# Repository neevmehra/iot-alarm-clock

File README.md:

# ECE445L Lab 4E - IoT Alarm Clock with MQTT and ESP8266

An embedded IoT alarm clock built on the **TM4C123 LaunchPad** with an **ESP8266 Wi-Fi module**, **MQTT-based communication**, and a **web application interface**. This project extends a prior clock system by enabling real-time remote monitoring and control over Wi-Fi.

## Overview
This project implements a “smart object” that publishes clock state to an MQTT broker and receives control commands from a web application. The system bridges embedded firmware, UART communication, Wi-Fi networking, and a browser-based frontend.

## Features
- Real-time clock displayed on the ST7735 LCD
- Remote control through MQTT publish/subscribe
- ESP8266 used as the Wi-Fi bridge between the TM4C123 and the broker
- Web app with clock controls:
  - Hour++
  - Hour--
  - Minute++
  - Minute--
  - Second++
  - Second--
  - Toggle 12/24-hour mode
- UART-based communication between TM4C123 and ESP8266
- Periodic state publishing from the board to the web app
- Subscription handling for incoming web commands
- Reuse and extension of prior clock/alarm functionality

## System Architecture
The data flow is:

TM4C123 -> UART -> ESP8266 -> Wi-Fi -> MQTT Broker -> Web App  
Web App -> MQTT Broker -> ESP8266 -> UART -> TM4C123

The TM4C publishes time data, and the web app sends back control commands using MQTT topics scoped to the user/team EID.

## Hardware
- TI EK-TM4C123GXL LaunchPad
- ESP8266-ESP01
- ST7735 TFT LCD
- External 3.3V regulator for ESP8266
- Switches
- Speaker / alarm hardware reused from Lab 3
- Supporting resistors, capacitors, MOSFET, diode, and wiring

## Software Components
### Embedded firmware
- TM4C123 firmware in C
- UART interface to ESP8266
- MQTT serialization/parsing support
- Clock/alarm logic and LCD update routines

### ESP8266 firmware
- Arduino-based firmware
- Wi-Fi connection handling
- MQTT broker connection
- Topic subscription and publication
- UART bridge between LaunchPad and MQTT broker

### Web application
- HTML / JavaScript MQTT client
- WebSocket-based broker communication
- Live time display and command buttons

## MQTT Interface
Example topic structure:

- `<eid>/b2w/mode`
- `<eid>/b2w/hour`
- `<eid>/b2w/min`
- `<eid>/b2w/sec`
- `<eid>/w2b`

Where:
- `b2w` = board to web
- `w2b` = web to board

## Key Technical Work
- Configured UART5 communication between the TM4C123 and ESP8266
- Modified parser logic for web-to-board commands
- Built CSV-based data transfer from TM4C firmware to the ESP8266
- Extended a browser MQTT app for remote clock control
- Integrated Lab 3 clock behavior into a networked IoT system
- Debugged timing, subscriptions, and state synchronization across devices

## Validation
This project was validated by:
- confirming broker connection from the ESP8266
- verifying topic publish/subscribe behavior
- checking synchronized updates on both the LCD and web interface
- testing remote control actions from the web app
- observing UART/debug output and timing behavior

## Repository Structure
```text
src/        TM4C123 firmware
esp/        ESP8266 Arduino code
web/        MQTT web application
docs/       images, diagrams, report assets
project/    Keil or IDE project files

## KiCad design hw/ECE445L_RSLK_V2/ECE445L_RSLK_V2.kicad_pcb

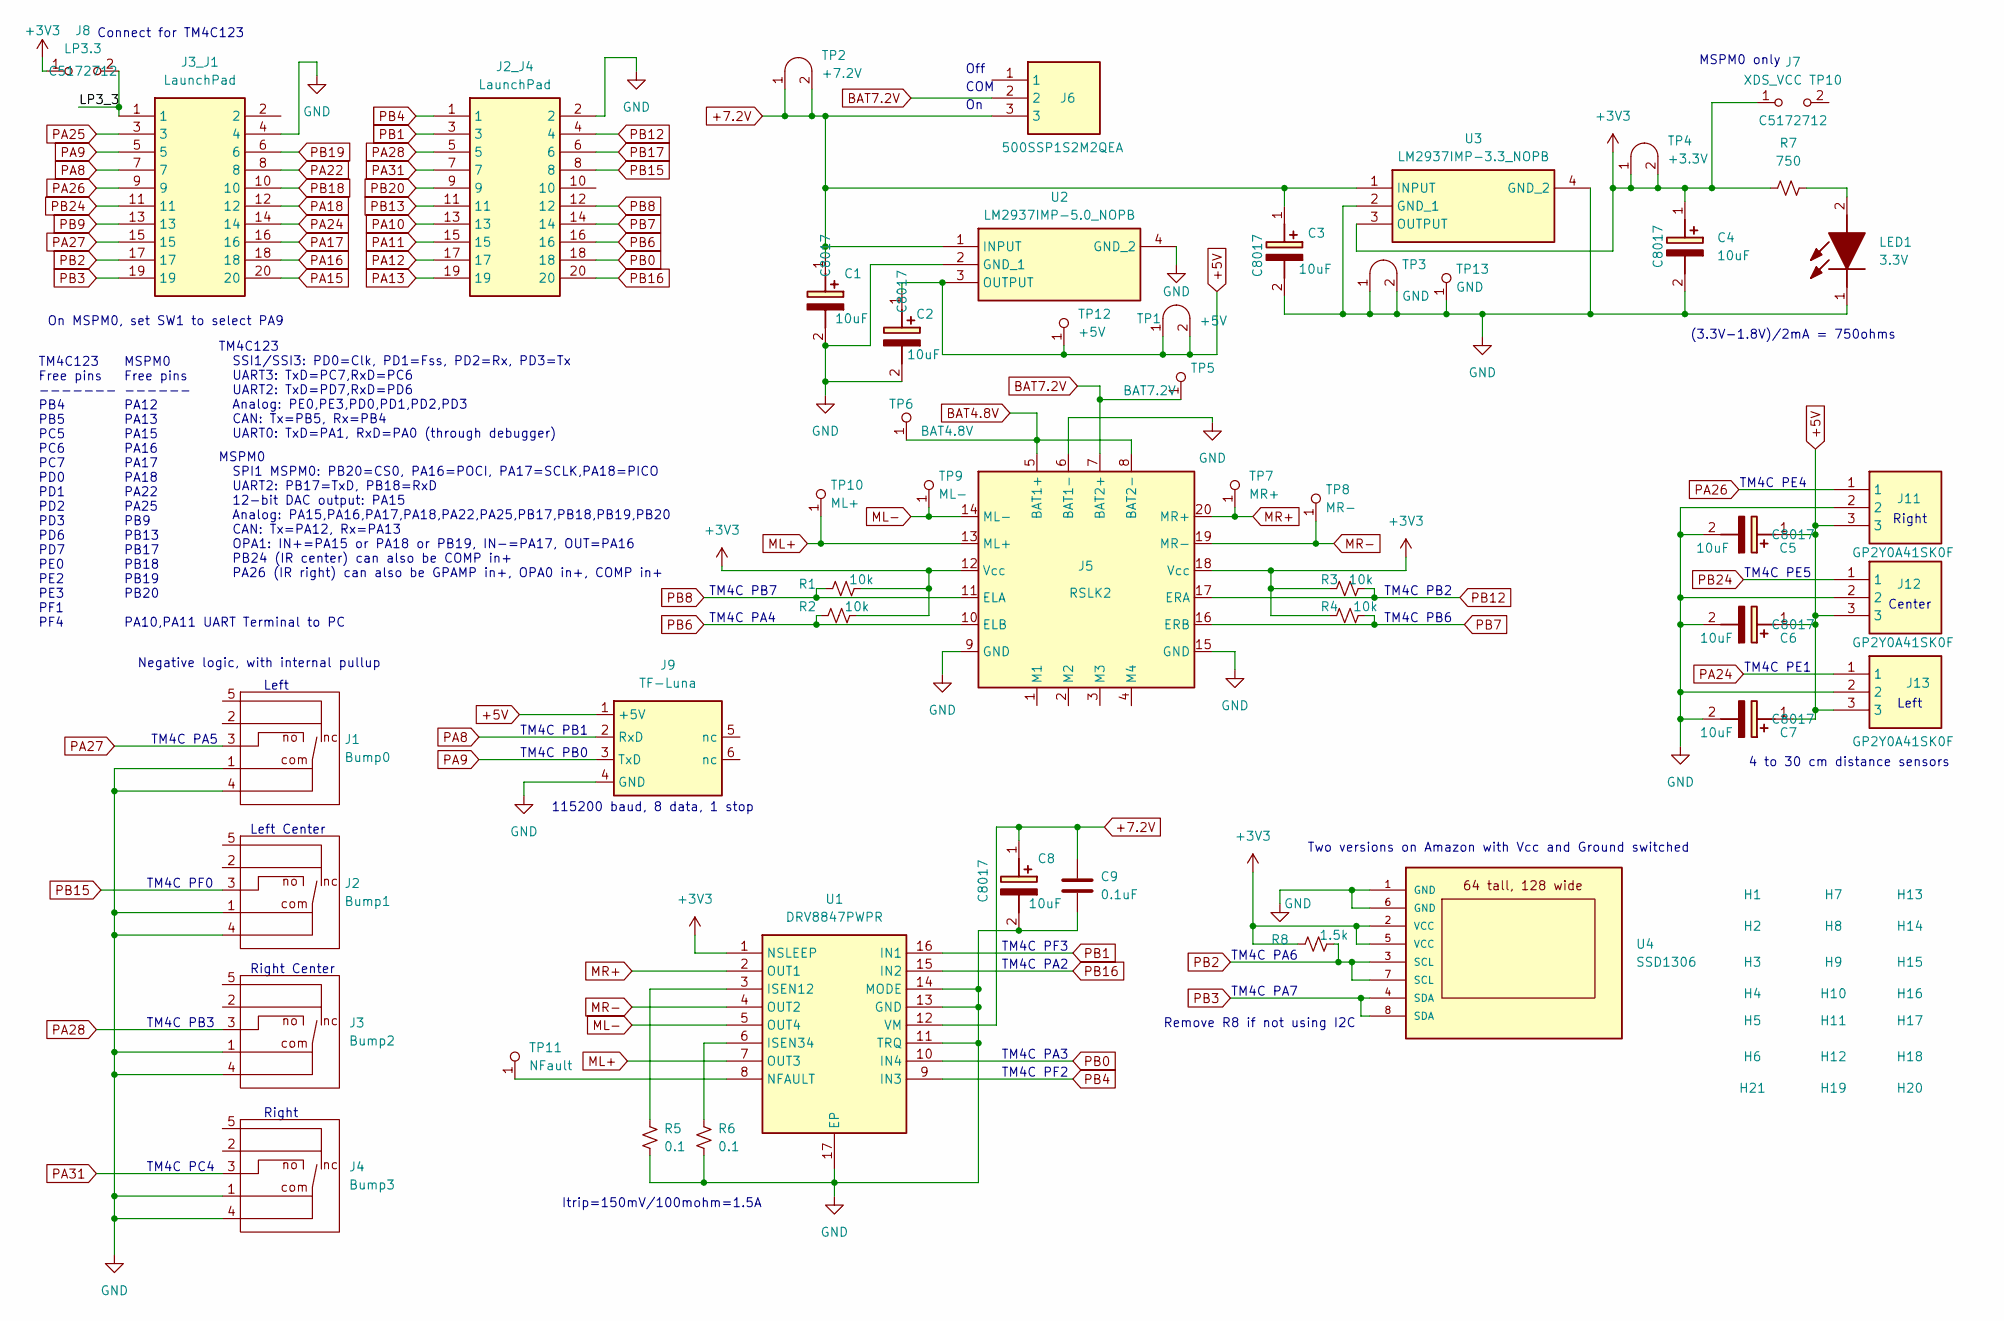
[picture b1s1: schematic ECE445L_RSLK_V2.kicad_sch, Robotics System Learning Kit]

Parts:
C1, C2, C3, C4, C5, C6, C7, C8: 10uF; CAPPM3528X210N; Mouser Part Number 581-TAJB106K020R
C9: 0.1uF; C_0603_1608Metric; LCSC C5186689
H1, H2, H3, H4, H5, H6, H7, H8, H9, H10, H11, H12, H13, H14, H15, H16, H17, H18, H19, H20, H21: MountingHole_4_40
J1: Bump0; D2F-01L30-D3_5pin
J2: Bump1; D2F-01L30-D3_5pin
J2_J4, J3_J1: LaunchPad; Mouser Part Number 855-M20-8761042P
J3: Bump2; D2F-01L30-D3_5pin
J4: Bump3; D2F-01L30-D3_5pin
J5: RSLK2; RSLK_Chassis
J6: 500SSP1S2M2QEA; Mouser Part Number 612-500SSP1S2M2QEA
J7: XDS_VCC TP10; PinHeader_1x02_P2.54mm_Vertical; LCSC C5172712
J8: LP3.3; PinHeader_1x02_P2.54mm_Vertical; LCSC C5172712
J9: TF-Luna; JST-GH_1x06_1.25mm
J11, J12, J13: GP2Y0A41SK0F; SHDR3W50P0X200_1X3_650X240X440P; Mouser Part Number 855-M22-7130342
LED1: 3.3V; APT1608CGCK; Mouser Part Number 604-APTD1608LSECKJ3F
R1, R2, R3, R4: 10k; R_0603_1608Metric; LCSC C340542
R5, R6: 0.1; R_1206_3216Metric; LCSC C2889036
R7: 750; R_0603_1608Metric; LCSC C365210
R8: 1.5k; R_0603_1608Metric; LCSC C216914
TP1: +5V; Testpoint_1x02_P2.54mm
TP2: +7.2V; Testpoint_1x02_P2.54mm
TP3: GND; Testpoint_1x02_P2.54mm
TP4: +3.3V; Testpoint_1x02_P2.54mm
TP5: BAT7.2V; Testpoint_1x1
TP6: BAT4.8V; Testpoint_1x1
TP7: MR+; Testpoint_1x1
TP8: MR-; Testpoint_1x1
TP9: ML-; Testpoint_1x1
TP10: ML+; Testpoint_1x1
TP11: NFault; Testpoint_1x1
TP12: +5V; Testpoint_1x1
TP13: GND; Testpoint_1x1
U1: DRV8847PWPR; SOP65P640X120-17N; Mouser Part Number 595-DRV8847PWPR
U2: LM2937IMP-5.0_NOPB; SOT230P700X180-4N; Mouser Part Number 926-LM2937IMP5.0NOPB
U3: LM2937IMP-3.3_NOPB; SOT230P700X180-4N; Mouser Part Number 926-LM2937IMP3.3NOPB
U4: SSD1306

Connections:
+3V3: C4.1 (+), J5.12 (Vcc), J5.18 (Vcc), J7.1 (A), J8.1 (A), R1.2, R2.2, R3.1, R4.1, R7.2, R8.1, TP4.1 (A), TP4.2 (B), U1.1 (NSLEEP), U3.3 (OUTPUT), U4.2 (VCC), U4.5 (VCC)
+5V: C2.1 (+), C5.1 (+), C6.1 (+), C7.1 (+), J9.1 (+5V), J11.3, J12.3, J13.3, TP1.1 (A), TP1.2 (B), TP12.1 (A), U2.3 (OUTPUT)
+7.2V: C1.1 (+), C3.1 (+), C8.1 (+), C9.1, J6.3, TP2.1 (A), TP2.2 (B), U1.12 (VM), U2.1 (INPUT), U3.1 (INPUT)
/LP3_3: J3_J1.1, J8.2 (B)
BAT4.8V: J5.5 (BAT1+), J5.8 (BAT2-), TP6.1 (A)
BAT7.2V: J5.7 (BAT2+), J6.2, TP5.1 (A)
GND: C1.2 (-), C2.2 (-), C3.2 (-), C4.2 (-), C5.2 (-), C6.2 (-), C7.2 (-), C8.2 (-), C9.2, J1.1 (com), J1.4 (com), J2.1 (com), J2.4 (com), J2_J4.2, J3.1 (com), J3.4 (com), J3_J1.4, J4.1 (com), J4.4 (com), J5.6 (BAT1-), J5.9 (GND), J5.15 (GND), J9.4 (GND), J11.2, J12.2, J13.2, LED1.1 (K), R5.2, R6.2, TP3.1 (A), TP3.2 (B), TP13.1 (A), U1.11 (TRQ), U1.13 (GND), U1.14 (MODE), U1.17 (EP), U2.2 (GND_1), U2.4 (GND_2), U3.2 (GND_1), U3.4 (GND_2), U4.1 (GND), U4.6 (GND)
ML+: J5.13 (ML+), TP10.1 (A), U1.7 (OUT3)
ML-: J5.14 (ML-), TP9.1 (A), U1.5 (OUT4)
MR+: J5.20 (MR+), TP7.1 (A), U1.2 (OUT1)
MR-: J5.19 (MR-), TP8.1 (A), U1.4 (OUT2)
unnamed: LED1.2 (A), R7.1
unnamed: TP11.1 (A), U1.8 (NFAULT)
unnamed: R5.1, U1.3 (ISEN12)
unnamed: R6.1, U1.6 (ISEN34)
PA8: J3_J1.7, J9.2 (RxD)
PA9: J3_J1.5, J9.3 (TxD)
PA10: J2_J4.13
PA11: J2_J4.15
PA12: J2_J4.17
PA13: J2_J4.19
PA15: J3_J1.20
PA16: J3_J1.18
PA17: J3_J1.16
PA18: J3_J1.12
PA22: J3_J1.8
PA24: J3_J1.14, J13.1
PA25: J3_J1.3
PA26: J3_J1.9, J11.1
PA27: J1.3 (no), J3_J1.15
PA28: J2_J4.5, J3.3 (no)
PA31: J2_J4.7, J4.3 (no)
PB0: J2_J4.18, U1.10 (IN4)
PB1: J2_J4.3, U1.16 (IN1)
PB2: J3_J1.17, R8.2, U4.3 (SCL), U4.7 (SCL)
PB3: J3_J1.19, U4.4 (SDA), U4.8 (SDA)
PB4: J2_J4.1, U1.9 (IN3)
PB6: J2_J4.16, J5.10 (ELB), R2.1
PB7: J2_J4.14, J5.16 (ERB), R4.2
PB8: J2_J4.12, J5.11 (ELA), R1.1
PB9: J3_J1.13
PB12: J2_J4.4, J5.17 (ERA), R3.2
PB13: J2_J4.11
PB15: J2.3 (no), J2_J4.8
PB16: J2_J4.20, U1.15 (IN2)
PB17: J2_J4.6
PB18: J3_J1.10
PB19: J3_J1.6
PB20: J2_J4.9
PB24: J3_J1.11, J12.1

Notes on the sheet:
TM4C PB7
TM4C PE5
Negative logic, with internal pullup
TM4C PF2
TM4C PC4
115200 baud, 8 data, 1 stop
Right
TM4C PA3
MSPM0 Free pins ------ PA12 PA13 PA15 PA16 PA17 PA18 PA22 PA25 PB9 PB13 PB17 PB18 PB19 PB20 PA10,PA11 UART Terminal to PC
TM4C PB2
TM4C123 Free pins ------- PB4 PB5 PC5 PC6 PC7 PD0 PD1 PD2 PD3 PD6 PD7 PE0 PE2 PE3 PF1 PF4
TM4C PA4
Left Center
Connect for TM4C123
Left
TM4C PF3
TM4C PA6
MSPM0 SPI1 MSPM0: PB20=CS0, PA16=POCI, PA17=SCLK,PA18=PICO UART2: PB17=TxD, PB18=RxD 12-bit DAC output: PA15 Analog: PA15,PA16,PA17,PA18,PA22,PA25,PB17,PB18,PB19,PB20 CAN: Tx=PA12, Rx=PA13 OPA1: IN+=PA15 or PA18 or PB19, IN-=PA17, OUT=PA16 PB24 (IR center) can also be COMP in+ PA26 (IR right) can a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
TM4C PB1
TM4C PF0
Two versions on Amazon with Vcc and Ground switched
Itrip=150mV/100mohm=1.5A
TM4C PA5
Off
4 to 30 cm distance sensors
TM4C PB6
On MSPM0, set SW1 to select PA9
Remove R8 if not using I2C
TM4C PB0
Right Center
Center
TM4C PE4
(3.3V-1.8V)/2mA = 750ohms
TM4C PB3
TM4C PA7
MSPM0 only
COM
TM4C PE1
TM4C PA2
TM4C123 SSI1/SSI3: PD0=Clk, PD1=Fss, PD2=Rx, PD3=Tx UART3: TxD=PC7,RxD=PC6 UART2: TxD=PD7,RxD=PD6 Analog: PE0,PE3,PD0,PD1,PD2,PD3 CAN: Tx=PB5, Rx=PB4 UART0: TxD=PA1, RxD=PA0 (through debugger)

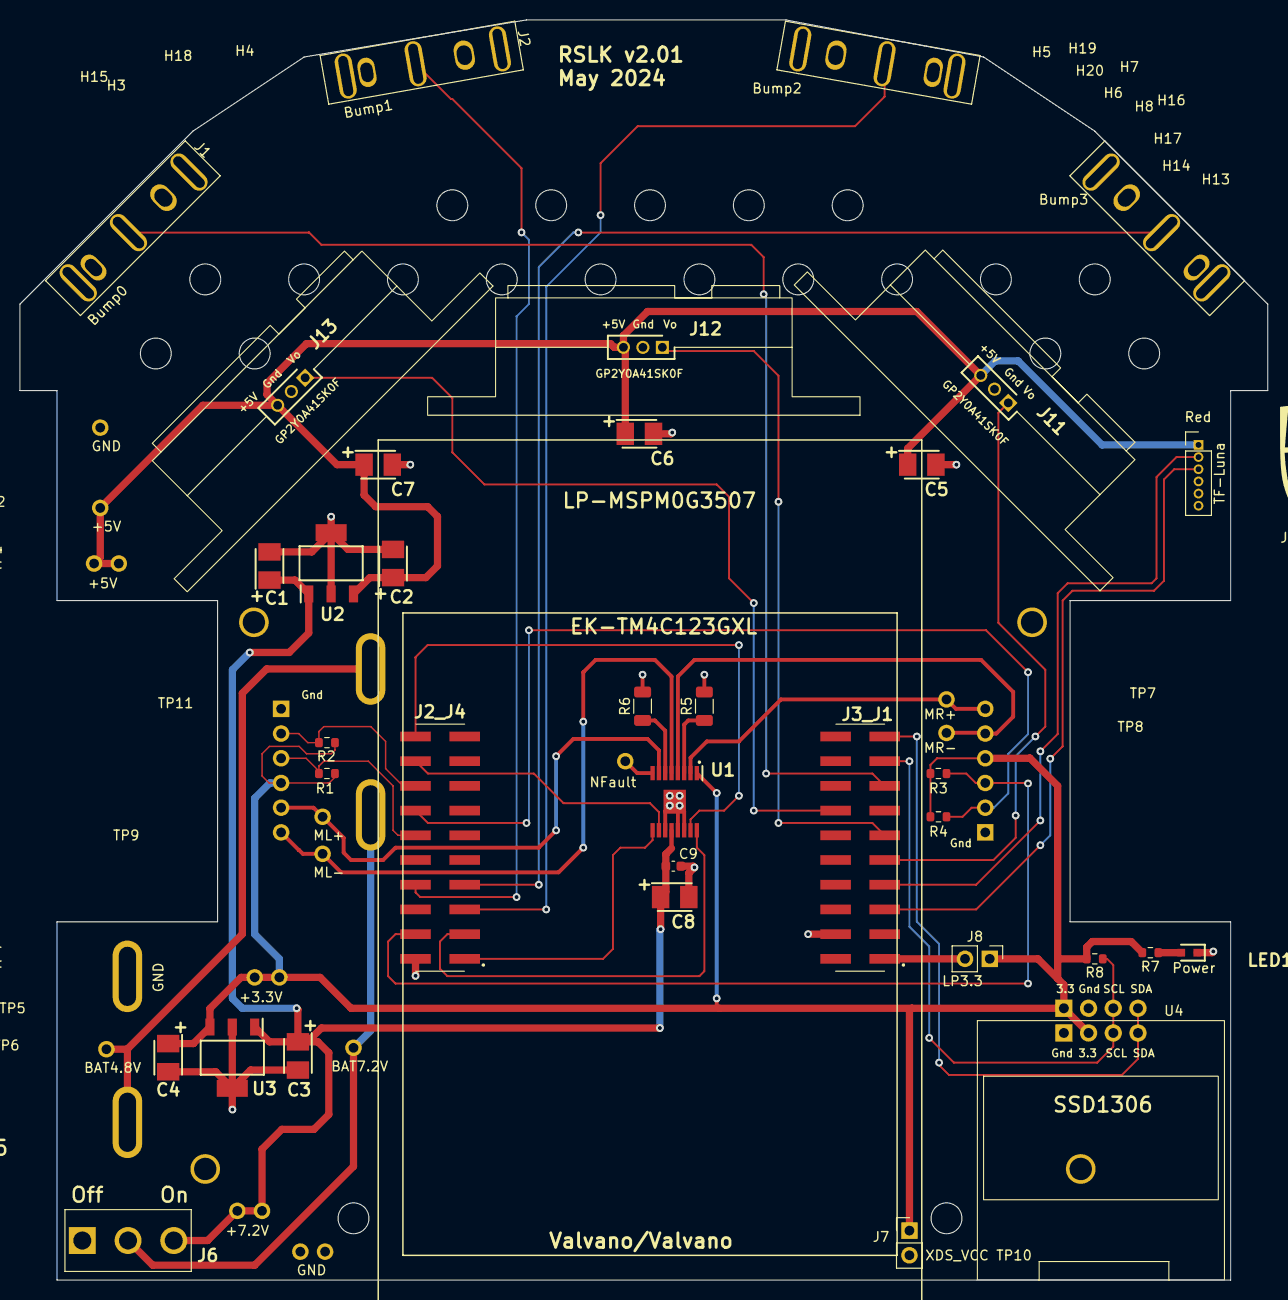
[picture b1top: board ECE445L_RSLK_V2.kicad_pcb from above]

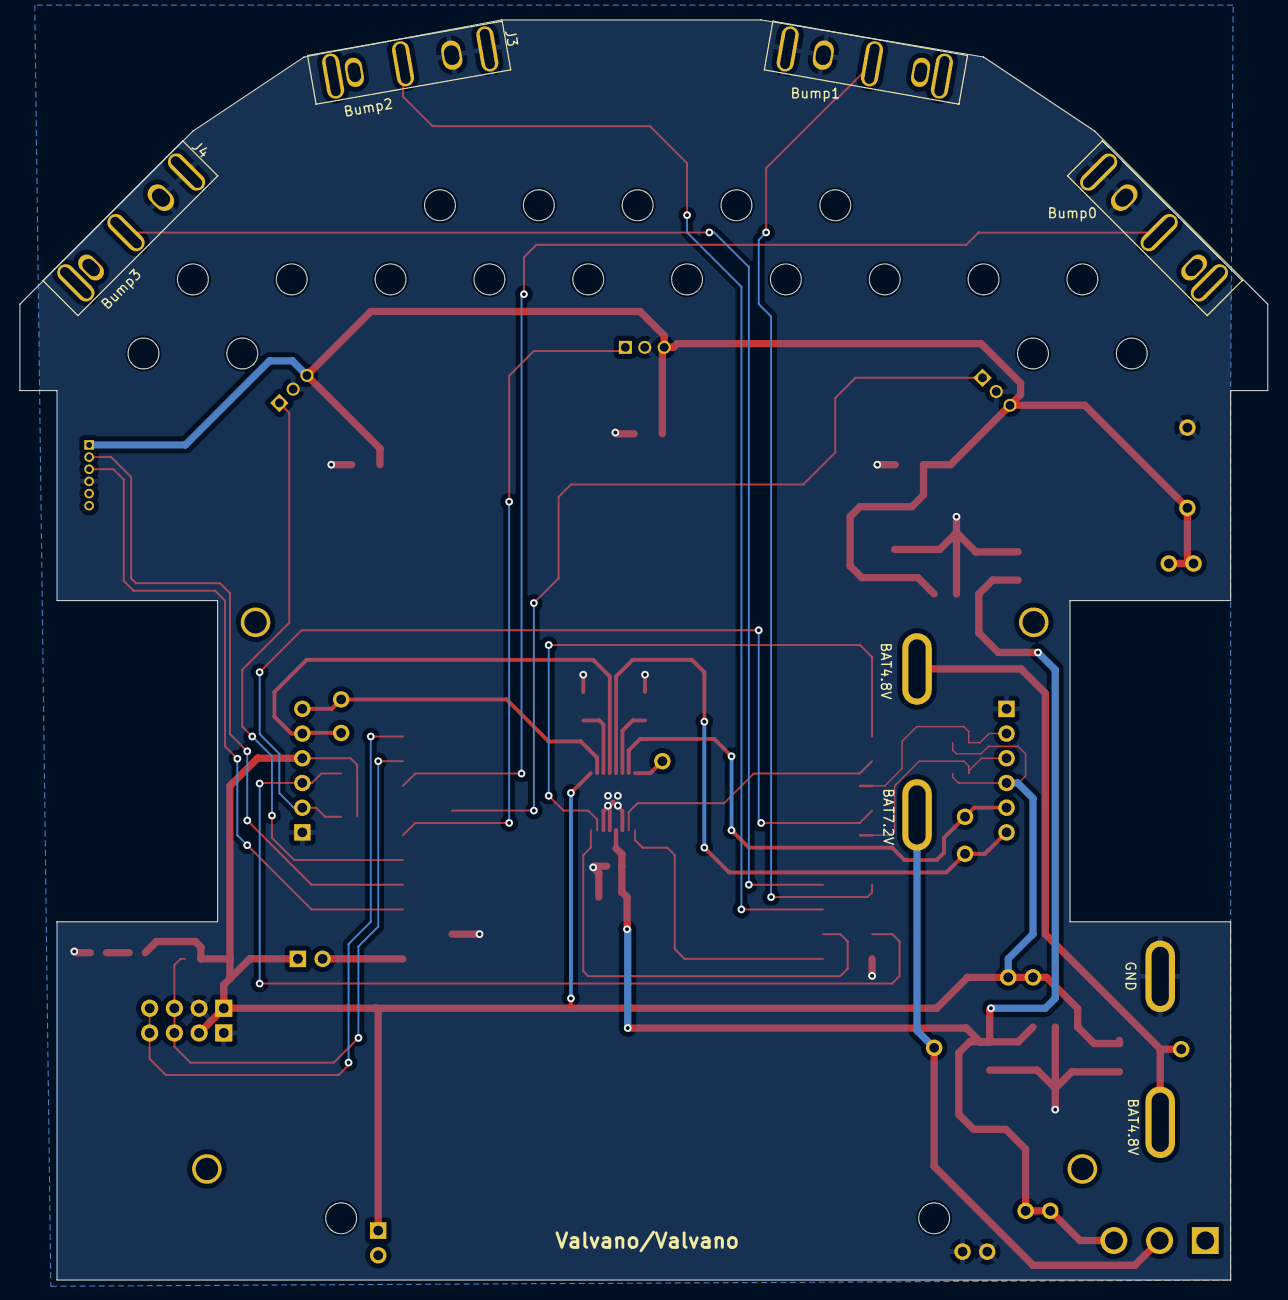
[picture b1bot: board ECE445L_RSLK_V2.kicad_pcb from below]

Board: 2 copper layers, 128.3 x 129.5 mm, 70 parts (2 on the bottom side), 34 nets.

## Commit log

2026-02-01 Flatten
2026-02-10 add deadline
2026-02-14 Initial changes
2026-02-14 New updates
2026-02-17 Checked out
2026-03-09 Initial public commit: ECE445L IoT Alarm Clock
